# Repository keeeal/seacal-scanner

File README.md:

# SEACAL Scanner
A 3D printable photogrammetry scanner for the Southeast Asian Ceramics Archaeology Laboratory.

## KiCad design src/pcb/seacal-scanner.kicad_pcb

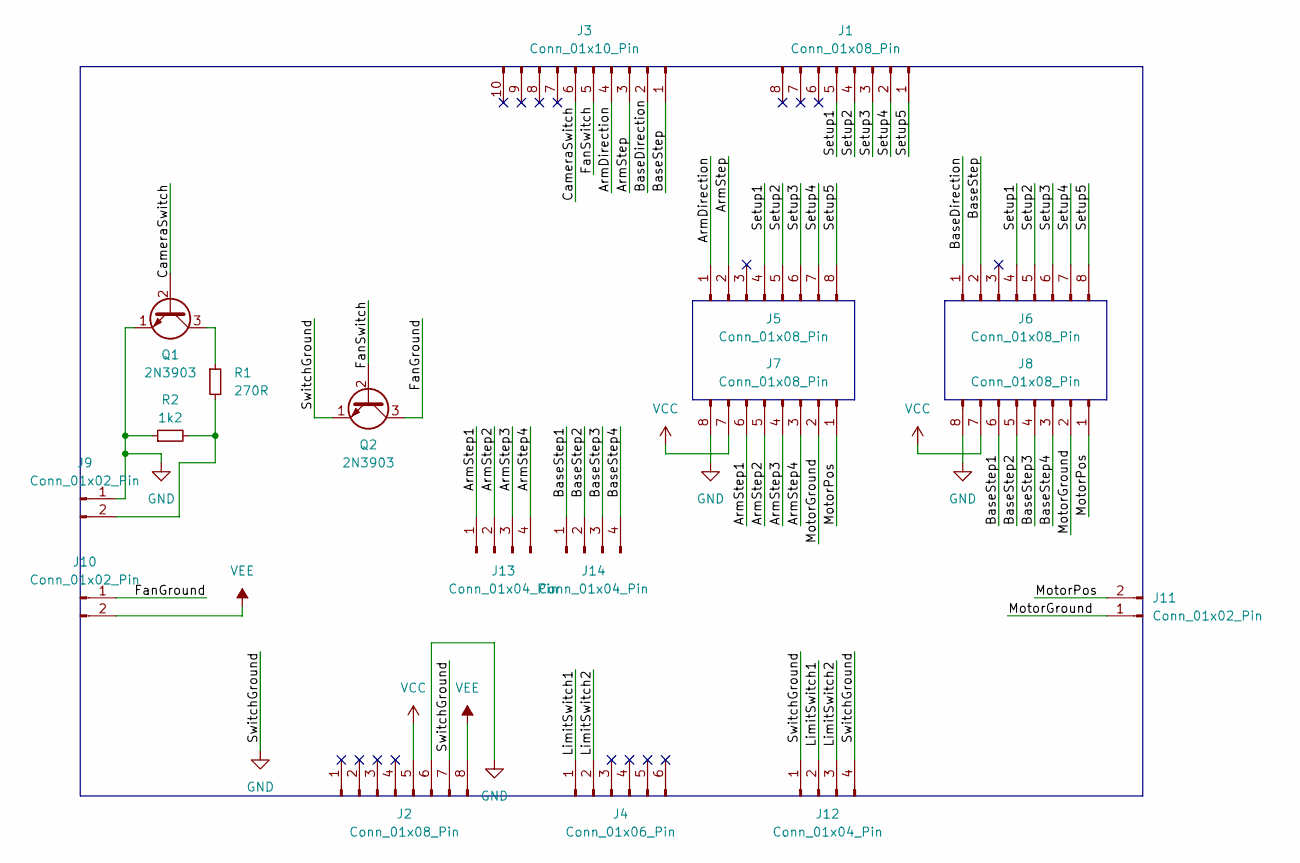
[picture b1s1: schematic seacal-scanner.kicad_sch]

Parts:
J1, J2, J5, J6, J7, J8: Conn_01x08_Pin; PinHeader_1x08_P2.54mm_Vertical
J3: Conn_01x10_Pin; PinHeader_1x10_P2.54mm_Vertical
J4: Conn_01x06_Pin; PinHeader_1x06_P2.54mm_Vertical
J9, J10, J11: Conn_01x02_Pin; PinHeader_1x02_P2.54mm_Vertical
J12, J13, J14: Conn_01x04_Pin; PinHeader_1x04_P2.54mm_Vertical
Q1, Q2: 2N3903; TO-92_Inline
R1: 270R; R_Axial_DIN0207_L6.3mm_D2.5mm_P10.16mm_Horizontal
R2: 1k2; R_Axial_DIN0207_L6.3mm_D2.5mm_P10.16mm_Horizontal

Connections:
/ArmDirection: J3.4, J5.1
/ArmStep: J3.3, J5.2
/ArmStep1: J7.6, J13.1
/ArmStep2: J7.5, J13.2
/ArmStep3: J7.4, J13.3
/ArmStep4: J7.3, J13.4
/BaseDirection: J3.2, J6.1
/BaseStep: J3.1, J6.2
/BaseStep1: J8.6, J14.1
/BaseStep2: J8.5, J14.2
/BaseStep3: J8.4, J14.3
/BaseStep4: J8.3, J14.4
/CameraSwitch: J3.6, Q1.2 (B)
/FanGround: J10.1, Q2.3 (C)
/FanSwitch: J3.5, Q2.2 (B)
/LimitSwitch1: J4.1, J12.2
/LimitSwitch2: J4.2, J12.3
/MotorGround: J7.2, J8.2, J11.1
/MotorPos: J7.1, J8.1, J11.2
/Setup1: J1.5, J5.4, J6.4
/Setup2: J1.4, J5.5, J6.5
/Setup3: J1.3, J5.6, J6.6
/Setup4: J1.2, J5.7, J6.7
/Setup5: J1.1, J5.8, J6.8
GND: J2.6, J2.7, J7.8, J8.8, J9.1, J12.1, J12.4, Q1.1 (E), Q2.1 (E), R2.1
unnamed: J9.2, R1.2, R2.2
unnamed: Q1.3 (C), R1.1
VCC: J2.5, J7.7, J8.7
VEE: J2.8, J10.2

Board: 2 copper layers, 18 parts (0 on the bottom side), 29 nets, no tracks yet.

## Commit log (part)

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2023-04-01 repo structure
2023-04-01 render_quality
2023-04-01 add base
2023-04-01 squircular base
2023-04-03 use herringbone gears
2023-04-18 add workflow
2023-04-19 reduce render quality in workflow
2023-04-19 add firmware workflow
2023-04-19 fix firmware workflow
2023-04-19 fix?
2023-04-19 restructure
2023-04-19 fix cad workflow?
2023-04-19 works?
2023-04-19 cli-compile-flags is list-like
2023-04-19 upload artifact
2023-04-19 echo $GITHUB_WORKSPACE
2023-04-19 clean up
2023-04-19 Save firmware binary (#2)
2023-04-22 adjust holes
2023-04-22 Adjust base-to-lazy-susan mounting holes (#32)
2023-04-24 update workflows
2023-04-24 also run if the workflow is modified
2023-04-24 Run workflows only when relevant files are modified (#36)
    * update workflows
    * also run if the workflow is modified
2023-04-24 submodule utils
2023-04-24 checkout with submodules recursive
2023-04-24 Submodule `cad/utils` (#42)
    * submodule utils
    * checkout with submodules recursive
2023-04-24 add dockerfile
2023-04-24 upload output/build/*.hex
2023-04-24 typo
2023-04-24 Add Dockerfile for firmware build (#43)
    * add dockerfile
2023-04-28 design foot
2023-04-28 designed apex
2023-04-28 foot with pocket
2023-04-28 Design axle
2023-04-28 thicken axle wall
2023-04-28 widen ribs
2023-04-28 fine tune axle
2023-04-28 add corner and cap
2023-04-28 --hardwarnings
2023-04-28 put submodule back
2023-04-28 Design camera arm joints (#52)
    * add foot
    * add apex
    * add axle
    * add corner
    * add cap
    * --hardwarnings on
2023-04-30 make script executable
2023-04-30 Split monolithic scad file into parts (#53)
    * restructure
2023-05-03 format check
2023-05-03 format
2023-05-03 Format checker (#56)
    * add format checker
    * format
2023-05-11 write Stepper.tick
2023-05-11 arduino requirements
2023-05-11 comment
2023-05-11 fix build
2023-05-13 Use AccelStepper library
2023-05-14 Create format service
2023-05-14 combine format checks
2023-05-14 rename jobs
2023-05-14 fix format job
2023-05-14 Format openscad code (#60)
    * Create format service
    * combine format checks
    * rename jobs
2023-05-26 Add gopro mount
2023-05-27 STL logs
2023-05-27 use pytest
2023-05-27 test-cad
2023-05-27 mkdir output
2023-05-27 archive logs
2023-05-27 pre-build cad service
2023-05-27 build -> pull
2023-05-27 network_mode: none
2023-05-28 Check that a single volume is created per STL (#64)
    * archive STL build logs
    * use pytest
    * add cad tests
2023-05-28 update openscad utils
2023-05-28 update cad utils
2023-05-28 Add gopro mount to attach a phone (#61)
    * Add gopro mount
    * update openscad utils
2023-05-28 add arm motor mount
2023-05-28 add wiring diagram
2023-05-28 only check format on code change
2023-05-28 Add arm motor mount (#65)
    * add arm motor mount
    * format
2023-05-28 Add wiring diagram (#66)
    * add wiring diagram
    * only check format on code change
2023-05-28 widen base
2023-05-28 Widen base (#67)
    * widen base
    * format
2023-05-28 Add badge
2023-05-28 gopro-mount $fn = 32
2023-05-28 Add badge (#68)
    * Add badge
    * gopro-mount $fn = 32
2023-05-29 update assembly
2023-05-29 update assembly (#72)
2023-05-31 add connector holes
2023-05-31 Add connector holes to arm motor mount (#77)
2023-06-08 separate parts + components dirs
2023-06-08 fix permission
2023-06-08 fix tests
2023-06-08 fix make format
2023-06-08 test_at_least_one_scad_file
2023-06-08 Separate parts and components (#81)
    * separate parts + components dirs
    * fix tests
    * test_at_least_one_scad_file
2023-06-09 add stop button
2023-06-09 Add stop button (#82)
2023-06-12 fix parts
2023-06-12 fix utils references
2023-06-12 build cad
2023-06-12 fix test cad
2023-06-12 update gitignore
2023-06-12 structure test
2023-06-12 fix platform
2023-06-12 update parts
2023-06-12 format tests
2023-06-12 Openscad recursive build system (#85)
    * add recursive build system
    * fix utils references
    * update gitignore
    * add structure tests
    * update parts file
    * format tests
2023-06-12 gx12 gx16 led-indicator limit-switch start-button
2023-06-12 test for uniqueness
2023-06-12 add control box
2023-06-12 test_no_fn_usage
2023-06-12 add $fn to customizer
2023-06-12 remove $fn
2023-06-12 update parts yaml
2023-07-01 use openscad-format
2023-07-01 attempt fix
2023-07-02 use isort
2023-07-02 format + test = dev
2023-07-02 render logs
2023-07-08 move conftest
2023-07-08 parts_config_file -> render_config_file
2023-07-08 fix test
2023-07-08 Use openscad-build and openscad-format (#88)
    * use openscad-build and openscad-format
    * format.Dockerfile + test.Dockerfile = dev.Dockerfile
2023-07-28 finish pcb
2023-08-13 update box and lid
2023-08-13 fix firmware archive
2023-08-13 Design control box (#86)
    * gx12 gx16 led-indicator limit-switch start-button
    * test for uniqueness
    * add control box
    * test_no_fn_usage
    * add $fn to customizer
    * remove $fn
2023-08-19 restructure frame
2023-08-19 add limit switch
2023-08-26 refactor makefile
2023-08-26 improve apex limit mount
2023-08-26 add limit switch mount
2023-08-27 update limit switch mounts
2023-08-27 Add top and bottom arm limiters (#94)
    * restructure frame
    * add limit switch
    * refactor makefile
    * improve apex limit mount
    * add limit switch mount
    * update limit switch mounts
2023-08-27 extend foot
2023-08-27 check stepper works
2023-08-27 fix render config
2023-08-27 Extend foot (#95)
    * extend foot
    * fix render config
2023-08-27 Add stepper class with acceleration control (#58)
    * write Stepper.tick
    * format
    * arduino requirements
    * comment
    * fix build
    * Use AccelStepper library
2023-08-27 add screw
2023-08-27 add states
2023-08-27 Add state machine (#98)
    * add states
2023-08-27 update axle and screw
2023-08-27 add phone clamp
2023-08-27 place in model
2023-08-27 Add screw to grip arm (#97)
    * add screw
    * add screw
    * update axle and screw
    * place in model
    * format
    * fix render config
2023-08-27 update credits
2023-08-27 Add phone clamp (#100)
    * add phone clamp
    * add stls
    * update credits
2023-09-02 use state machine library
2023-09-17 write homing sequence
2023-09-21 Use state machine library (#103)
    * use state machine library
    * write homing sequence
    * clean up
2023-10-22 Add kicad breakout
2024-02-19 add scan sequence
2024-02-19 add scan sequence (#104)
2024-02-20 button class, camera class, stepper settings, fix scan
2024-02-20 make StepMode public
2024-02-20 Add button class, camera class, stepper settings (#111)
    * button class, camera class, stepper settings, fix scan
2024-02-20 simplify base
2024-02-20 simplify base (#115)
2024-02-23 add screw to arm motor mount (#117)
2024-02-23 add screw to phone mount (#118)
2024-02-25 add clip
2024-02-25 fan control
2024-02-25 fan control (#121)
2024-02-25 add start button behaviour
2024-02-25 add start button behaviour (#122)
2024-02-25 update lid
2024-02-25 add emergency stop
2024-02-25 change pin
2024-02-25 add emergency stop (#123)
2024-02-25 add cable clip (#120)
2024-02-25 add pulley
2024-02-27 minor tweaks
2024-02-28 add text to lid
2024-03-01 fix tolerance
2024-03-01 update settings
2024-03-01 update settings (#124)
2024-03-01 Add pulley (#101)
2024-03-01 update control box (#119)
2024-03-05 add release workflow
2024-03-05 add release workflow (#131)
2024-03-05 Fix release.yaml (#132)
2024-03-05 generate gerbers
2024-03-05 fix cad test utils
2024-03-06 user: root
2024-03-06 generate gerbers (#133)
2024-03-06 Fix release.yaml
2024-03-09 move limit switch
2024-03-10 move limit switch (#138)
2024-03-10 fix motor mount screw hole (#144)
2024-06-25 spiral path
2024-06-25 remove spiral
2026-04-28 add ui
2026-05-08 add sequence to app
2026-05-08 ping?
2026-05-08 read?
2026-06-10 multi-photo + shutter delay
2026-06-10 update pcb tests
2026-06-10 add arduino-cli
2026-06-10 firmware tests
2026-06-10 appease clippy
2026-06-10 formate firmware
2026-06-10 fix fw wf
2026-06-10 Add UI and use USB camera (#156)
